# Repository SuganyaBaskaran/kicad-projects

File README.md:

# kicad-projects
Portfolio, learning and practice attempts using KiCAD.

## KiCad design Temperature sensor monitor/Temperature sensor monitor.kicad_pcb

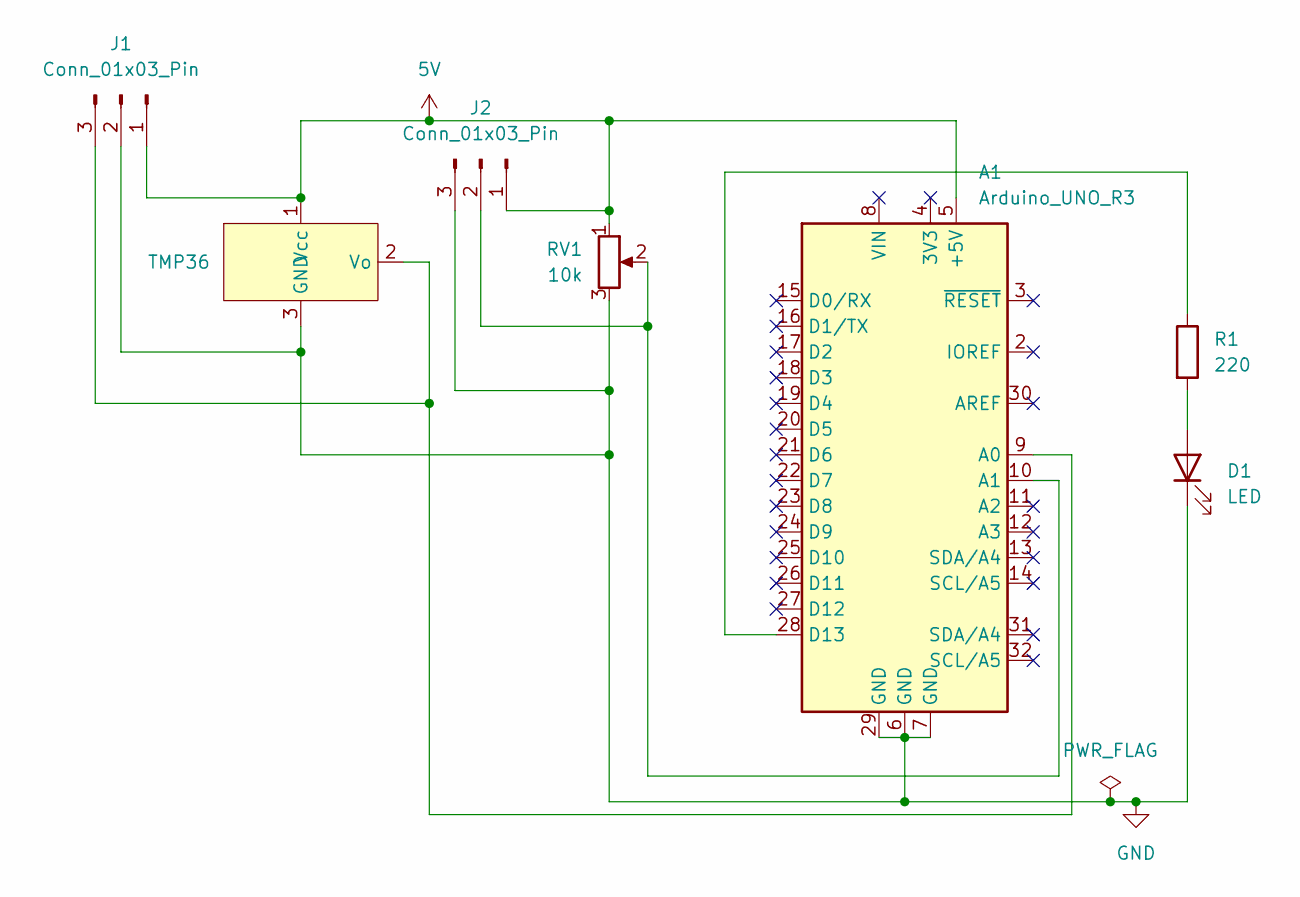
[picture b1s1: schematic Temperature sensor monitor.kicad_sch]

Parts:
A1: Arduino_UNO_R3
D1: LED; LED_D5.0mm
J1, J2: Conn_01x03_Pin; PinHeader_1x03_P2.54mm_Vertical
R1: 220; R_Axial_DIN0207_L6.3mm_D2.5mm_P7.62mm_Horizontal
RV1: 10k; Potentiometer_Bourns_3386P_Vertical
U1: TMP36; TO-92

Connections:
5V: A1.5 (+5V), J1.1, J2.1, RV1.1, U1.1 (Vcc)
GND: A1.6 (GND), A1.7 (GND), A1.29 (GND), D1.1 (K), J1.2, J2.3, RV1.3, U1.3 (GND)
unnamed: A1.9 (A0), J1.3, U1.2 (Vo)
unnamed: A1.10 (A1), J2.2, RV1.2
unnamed: A1.28 (D13), R1.1
unnamed: D1.2 (A), R1.2

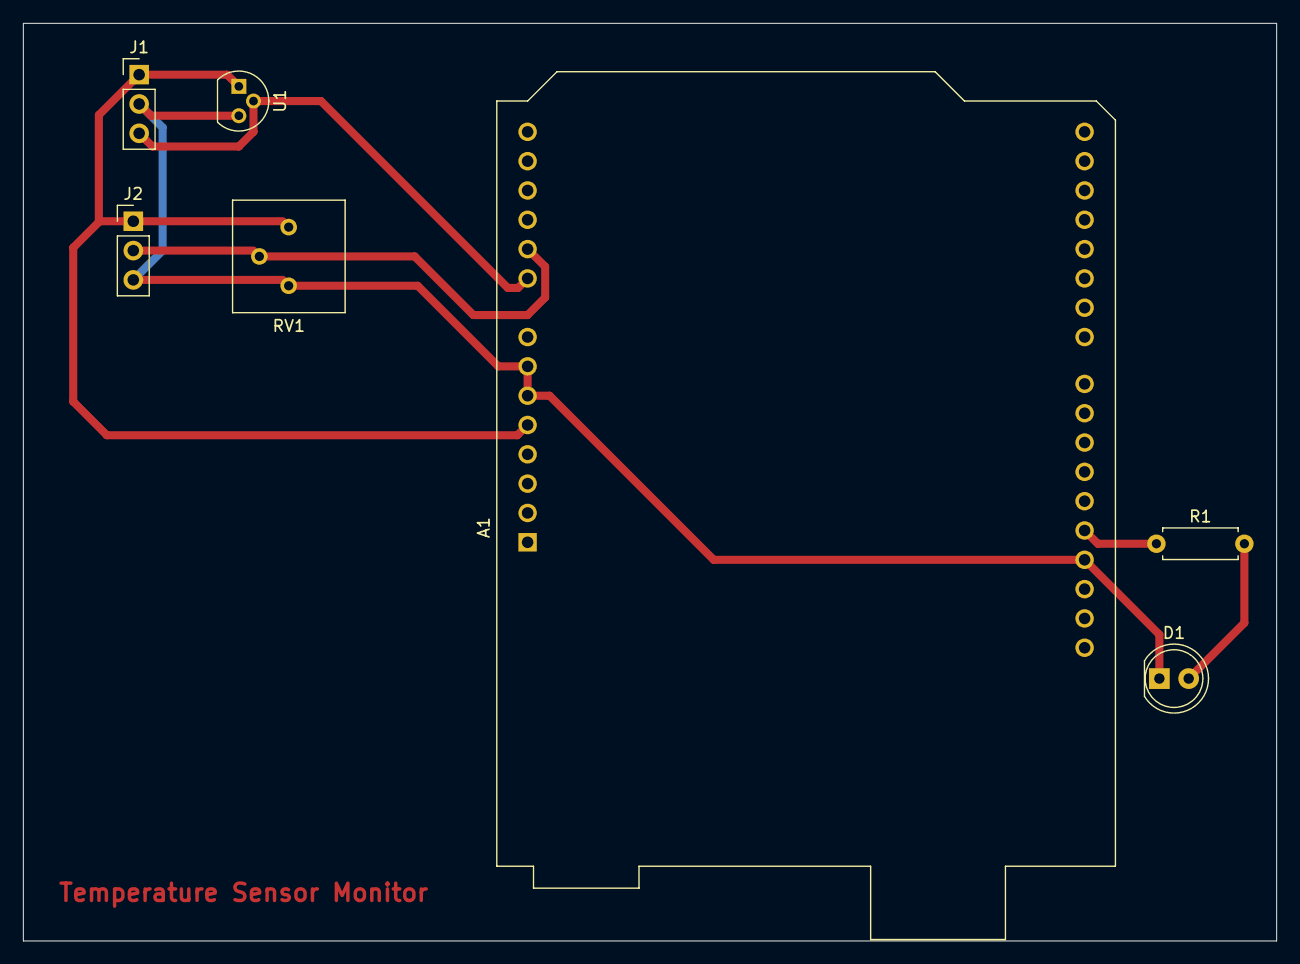
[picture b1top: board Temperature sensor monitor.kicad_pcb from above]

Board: 4 copper layers, 108.6 x 79.5 mm, 7 parts (0 on the bottom side), 6 nets.

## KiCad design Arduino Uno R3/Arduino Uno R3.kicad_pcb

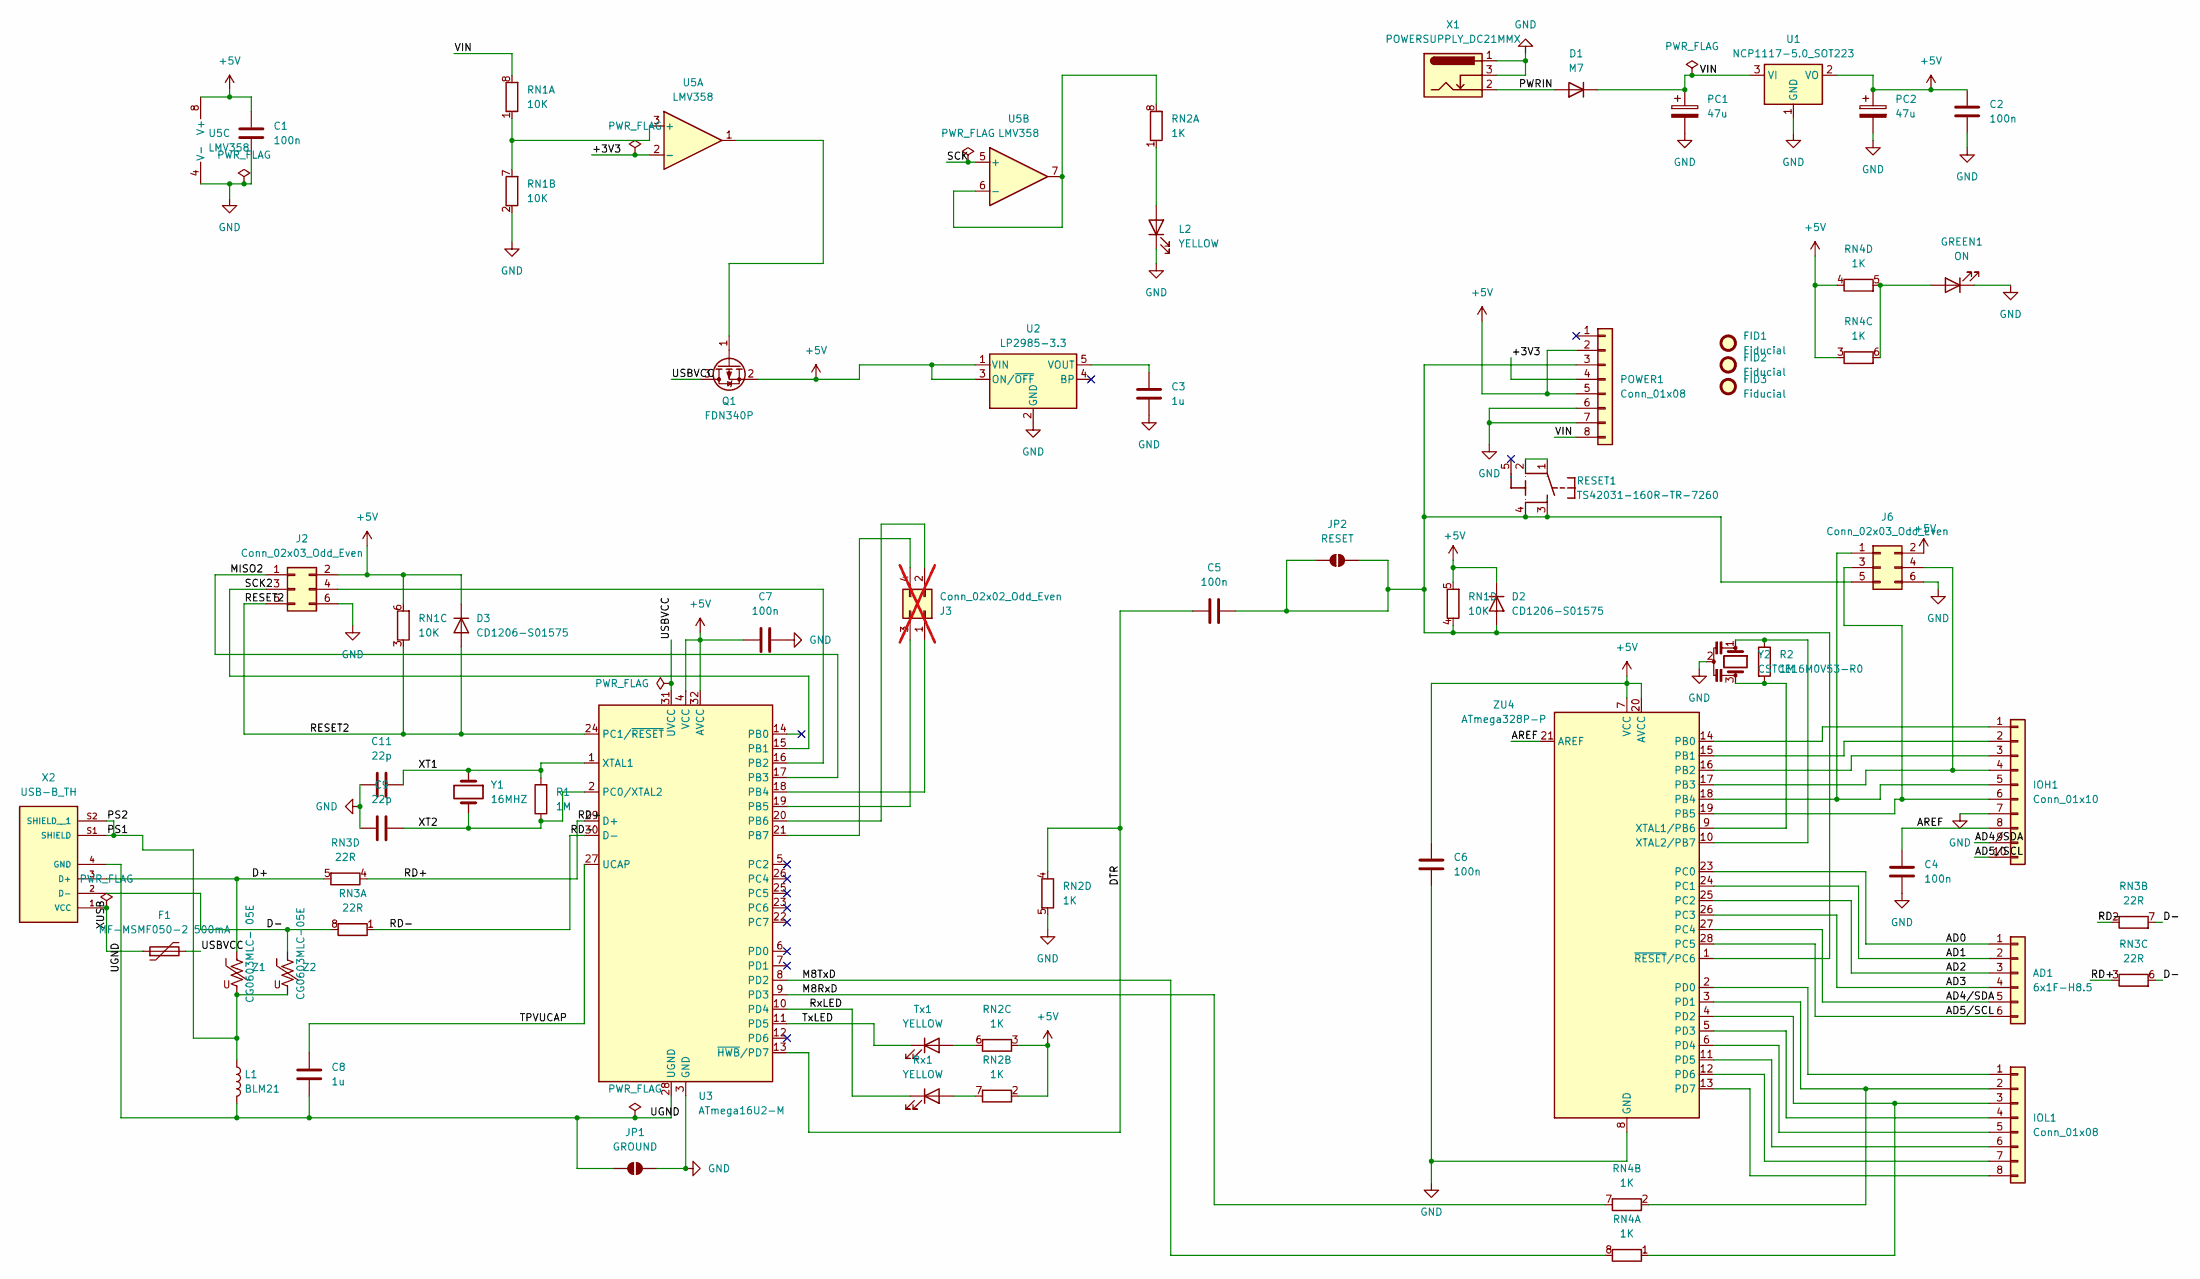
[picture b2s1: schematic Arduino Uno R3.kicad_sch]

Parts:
AD1: 6x1F-H8.5; PinSocket_1x06_P2.54mm_Vertical
C1, C2, C4, C5, C6, C7: 100n; C_0603_1608Metric
C3, C8: 1u; C_0603_1608Metric
C9, C11: 22p; C_0603_1608Metric
D1: M7; D_SMB
D2, D3: CD1206-S01575; D_1206_3216Metric
F1: MF-MSMF050-2 500mA; FUSM4632X85
FID1, FID2, FID3: Fiducial; Fiducial_1mm_Mask3mm
GREEN1: ON; LED_0805_2012Metric
IOH1: Conn_01x10; PinSocket_1x10_P2.54mm_Vertical
IOL1: Conn_01x08; PinSocket_1x08_P2.54mm_Vertical
J2, J6: Conn_02x03_Odd_Even; PinHeader_2x03_P2.54mm_Vertical
J3: Conn_02x02_Odd_Even; PinHeader_2x02_P2.54mm_Vertical; not fitted
JP1: GROUND; SolderJumper-2_P1.3mm_Open_Pad1.0x1.5mm
JP2: RESET; SolderJumper-2_P1.3mm_Open_Pad1.0x1.5mm
L1: BLM21; L_0805_2012Metric
L2: YELLOW; LED_0805_2012Metric
PC1, PC2: 47u; CP_Elec_6.3x4.9
POWER1: Conn_01x08; PinSocket_1x08_P2.54mm_Vertical
Q1: FDN340P; SOT-23
R1, R2: 1M; R_0603_1608Metric
RESET1: TS42031-160R-TR-7260; TS42
RN1: 10K; R_Array_Concave_4x0603
RN2, RN4: 1K; R_Array_Concave_4x0603
RN3: 22R; R_Array_Concave_4x0603
Rx1: YELLOW; LED_0805_2012Metric
Tx1: YELLOW; LED_0805_2012Metric
U1: NCP1117-5.0_SOT223; SOT-223-3_TabPin2
U2: LP2985-3.3; SOT-23-5
U3: ATmega16U2-M; QFN-32-1EP_5x5mm_P0.5mm_EP3.6x3.6mm
U5: LMV358; TSSOP-8_4.4x3mm_P0.65mm
X1: POWERSUPPLY_DC21MMX; BarrelJack_Horizontal
X2: USB-B_TH; AMPHENOL_61729-1011BLF; PARTREV AB
Y1: 16MHZ; Crystal_HC49-U_Vertical
Y2: CSTCE16M0V53-R0; Resonator_SMD_Murata_CSTxExxV-3Pin_3.0x1.1mm
Z1: CG0603MLC- 05E; VARC1608X56N
Z2: CG0603MLC-05E; VARC1608X56N
ZU4: ATmega328P-P; DIP-28_W7.62mm

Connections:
+5V: C1.1, C2.1, C6.1, C7.1, D2.1 (K), D3.1 (K), J2.2, J6.2, PC2.1, POWER1.2, POWER1.5, Q1.2 (S), RN1.5 (R4.2), RN1.6 (R3.2), RN2.2 (R2.1), RN2.3 (R3.1), RN4.3 (R3.1), RN4.4 (R4.1), U1.2 (VO), U2.1 (VIN), U2.3 (ON/~OFF), U3.4 (VCC), U3.32 (AVCC), U5.8 (V+), ZU4.7 (VCC), ZU4.20 (AVCC)
/+3V3: POWER1.4, U5.2 (-)
/AD0: AD1.1, ZU4.23 (PC0)
/AD1: AD1.2, ZU4.24 (PC1)
/AD2: AD1.3, ZU4.25 (PC2)
/AD3: AD1.4, ZU4.26 (PC3)
/AD4/SDA: AD1.5, IOH1.9, ZU4.27 (PC4)
/AD5/SCL: AD1.6, IOH1.10, ZU4.28 (PC5)
/AREF: C4.1, IOH1.8, ZU4.21 (AREF)
/D+: RN3.5 (R4.2), X2.3 (D+), Z1.1
/D-: RN3.6 (R3.2), RN3.7 (R2.2), RN3.8 (R1.2), X2.2 (D-), Z2.1
/DTR: C5.1, RN2.4 (R4.1), U3.13 (~HWB/PD7)
/M8RxD: RN4.7 (R2.2), U3.9 (PD3)
/M8TxD: RN4.8 (R1.2), U3.8 (PD2)
/MISO2: J2.1, U3.17 (PB3)
/PS1: L1.1, X2.S1 (SHIELD), X2.S2 (SHIELD__1), Z1.2, Z2.2
/PWRIN: D1.2 (A), X1.2
/RD+: RN3.3 (R3.1), RN3.4 (R4.1), U3.29 (D+)
/RD-: RN3.1 (R1.1), RN3.2 (R2.1), U3.30 (D-)
/RESET2: D3.2 (A), J2.5, RN1.3 (R3.1), U3.24 (PC1/~RESET)
/RxLED: Rx1.1 (K), U3.10 (PD4)
/SCK: U5.5 (+)
/SCK2: J2.3, U3.15 (PB1)
/TPVUCAP: C8.1, U3.27 (UCAP)
/TxLED: Tx1.1 (K), U3.11 (PD5)
/UGND: C8.2, JP1.1 (A), L1.2, U3.28 (UGND), X2.4 (GND)
/USBVCC: F1.2, Q1.3 (D), U3.31 (UVCC)
/VIN: D1.1 (K), PC1.1, POWER1.8, RN1.8 (R1.2), U1.3 (VI)
/XT1: C11.2, R1.2, U3.1 (XTAL1), Y1.1
/XT2: C9.2, R1.1, U3.2 (PC0/XTAL2), Y1.2
/XUSB: F1.1, X2.1 (VCC)
GND: C1.2, C2.2, C3.2, C4.2, C6.2, C7.2, C9.1, C11.1, GREEN1.1 (K), IOH1.7, J2.6, J6.6, JP1.2 (B), L2.1 (K), PC1.2, PC2.2, POWER1.6, POWER1.7, RN1.2 (R2.1), RN2.5 (R4.2), U1.1 (GND), U2.2 (GND), U3.3 (GND), U3.33 (GND), U5.4 (V-), X1.1, X1.3, Y2.2, ZU4.8 (GND), ZU4.22 (GND)
unnamed: C5.2, D2.2 (A), J6.5, JP2.1 (A), JP2.2 (B), POWER1.3, RESET1.3, RESET1.4, RN1.4 (R4.1), ZU4.1 (~RESET/PC6)
unnamed: GREEN1.2 (A), RN4.5 (R4.2), RN4.6 (R3.2)
unnamed: IOH1.1, ZU4.14 (PB0)
unnamed: IOH1.2, ZU4.15 (PB1)
unnamed: IOH1.3, ZU4.16 (PB2)
unnamed: IOH1.4, J6.4, ZU4.17 (PB3)
unnamed: IOH1.5, J6.1, ZU4.18 (PB4)
unnamed: IOH1.6, J6.3, ZU4.19 (PB5)
unnamed: IOL1.1, ZU4.2 (PD0)
unnamed: IOL1.2, RN4.2 (R2.1), ZU4.3 (PD1)
unnamed: IOL1.3, RN4.1 (R1.1), ZU4.4 (PD2)
unnamed: IOL1.4, ZU4.5 (PD3)
unnamed: IOL1.5, ZU4.6 (PD4)
unnamed: IOL1.6, ZU4.11 (PD5)
unnamed: IOL1.7, ZU4.12 (PD6)
unnamed: IOL1.8, ZU4.13 (PD7)
unnamed: J2.4, U3.16 (PB2)
unnamed: J3.1, U3.18 (PB4)
unnamed: J3.2, U3.20 (PB6)
unnamed: J3.3, U3.19 (PB5)
unnamed: J3.4, U3.21 (PB7)
unnamed: L2.2 (A), RN2.1 (R1.1)
unnamed: Q1.1 (G), U5.1
unnamed: RESET1.1, RESET1.2
unnamed: RN1.1 (R1.1), RN1.7 (R2.2), U5.3 (+)
unnamed: RN2.8 (R1.2), U5.6 (-), U5.7
unnamed: RN2.7 (R2.2), Rx1.2 (A)
unnamed: RN2.6 (R3.2), Tx1.2 (A)
unnamed: C3.1, U2.5 (VOUT)
unnamed: R2.2, Y2.3, ZU4.9 (XTAL1/PB6)
unnamed: R2.1, Y2.1, ZU4.10 (XTAL2/PB7)

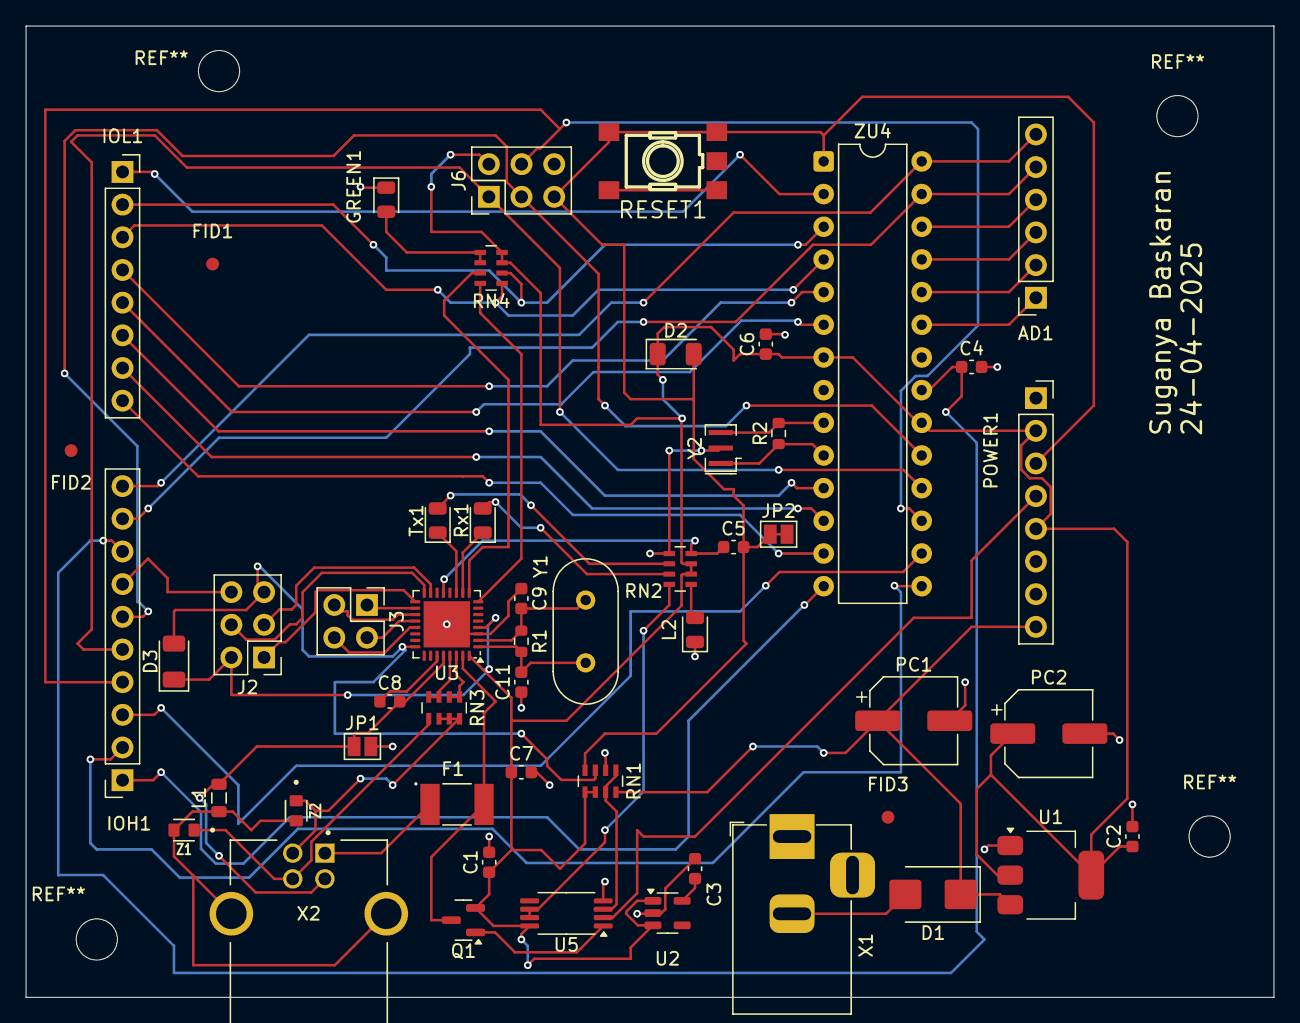
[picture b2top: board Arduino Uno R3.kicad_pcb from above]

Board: 2 copper layers, 97.0 x 75.5 mm, 52 parts (0 on the bottom side), 62 nets.

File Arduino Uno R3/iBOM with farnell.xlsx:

Ref | Value | Footprint | Quantity | Farnell id | SMD/THT
C1, C2, C4, C5, C6, C7 | 100n | C_0603_1608Metric | 6 | 3288318 | SMD
C3, C8 | 1u | C_0603_1608Metric | 2 | 2118128 | SMD
C9, C11 | 22p | C_0603_1608Metric | 2 | 3508850 | SMD
R1, R2 | 1M | R_0603_1608Metric | 2 | 3579860 | SMD
L2, Rx1, Tx1 | YELLOW | LED_0805_2012Metric | 3 | 1318246 | SMD
L1 | BLM21 | L_0805_2012Metric | 1 | 3227824 | SMD
D2, D3 | CD1206-S01575 | D_1206_3216Metric | 2 | 652-CD1206-S01575(Mouser) | SMD
D1 | M7 | D_SMB | 1 | 3127427 | SMD
U1 | NCP1117-5.0_SOT223 | SOT-223-3_TabPin2 | 1 | 2112617 | SMD
U2 | LP2985-3.3 | SOT-23-5 | 1 | 3007616 | SMD
U3 | ATmega16U2-M | QFN-32-1EP_5x5mm_P0.5mm_EP3.6x3.6mm | 1 | 2810000 | SMD
U5 | LMV358 | TSSOP-8_4.4x3mm_P0.65mm | 1 | 2806805 | SMD
Y1 | 16MHZ | Crystal_HC49-U_Vertical | 1 | 9712860 | THT
Y2 | CSTCE16M0V53-R0 | Resonator_SMD_Murata_CSTxExxV-3Pin_3.0x1.1mm | 1 | 2443265 | SMD
X1 | POWERSUPPLY_DC21MMX | BarrelJack_Horizontal | 1 | 224959 | THT
X2 | USB-B_TH | AMPHENOL_61729-1011BLF | 1 | 2668483 | THT
F1 | MF-MSMF050-2 500mA | FUSM4632X85 | 1 | 9350314 | SMD
IOL1, POWER1 | Conn_01x08 | PinSocket_1x08_P2.54mm_Vertical | 2 | 3583755 | THT
PC1, PC2 | 47u | CP_Elec_6.3x4.9 | 2 | 3227549 | SMD
RN2, RN4 | 1K | R_Array_Concave_4x0603 | 2 | 2060162 | SMD
AD1 | 6x1F-H8.5 | PinSocket_1x06_P2.54mm_Vertical | 1 | 2827893 | THT
GREEN1 | ON | LED_0805_2012Metric | 1 | 2290331 | SMD
IOH1 | Conn_01x10 | PinSocket_1x10_P2.54mm_Vertical | 1 | 1841230 | THT
Q1 | FDN340P | SOT-23 | 1 | 9846310 | SMD
RESET1 | TS42031-160R-TR-7260 | TS42 | 1 | 506-FSMSMLPATR(Mouser) | SMD
RN1 | 10K | R_Array_Concave_4x0603 | 1 | 2060167 | SMD
RN3 | 22R | R_Array_Concave_4x0603 | 1 | 2060150 | SMD
Z1 | CG0603MLC-05E | VARC1608X56N | 1 | 1838966 | SMD
Z2 | CG0603MLC-05E | VARC1608X56N | 1 | 1838966 | SMD
ZU4 | ATmega328P-P | DIP-28_W7.62mm | 1 | 2443179 | THT
J2, J6 | Conn_02x03_Odd_Even | PinHeader_2x03_P2.54mm_Vertical | 2 | 2356131 | THT

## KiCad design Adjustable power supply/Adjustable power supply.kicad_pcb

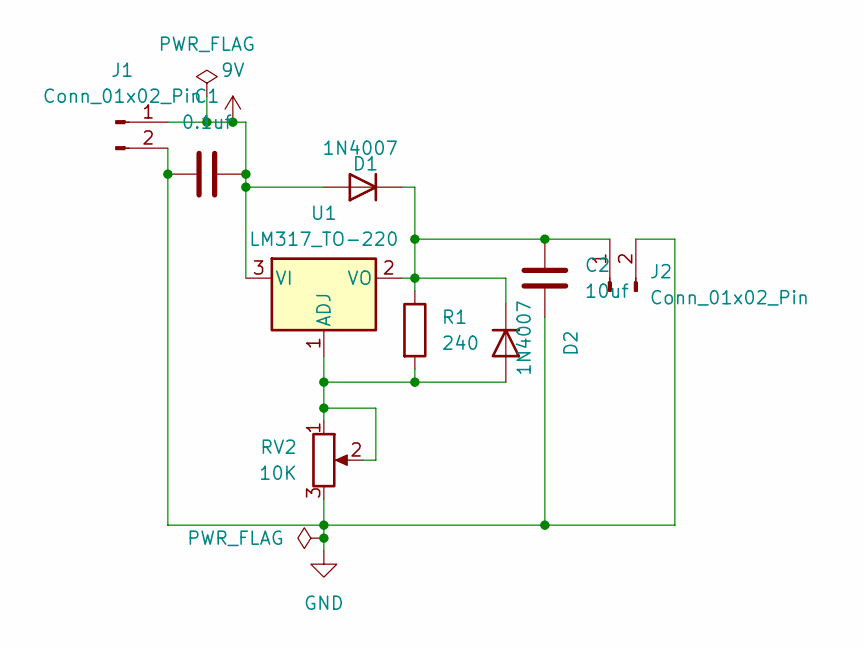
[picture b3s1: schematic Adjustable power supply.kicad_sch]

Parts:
C1: 0.1uf; C_Disc_D3.0mm_W1.6mm_P2.50mm
C2: 10uf; C_Disc_D3.0mm_W1.6mm_P2.50mm
D1, D2: 1N4007; D_DO-41_SOD81_P10.16mm_Horizontal
J1, J2: Conn_01x02_Pin; TerminalBlock_bornier-2_P5.08mm
R1: 240; R_Axial_DIN0207_L6.3mm_D2.5mm_P2.54mm_Vertical
RV2: 10K; Potentiometer_Alpha_RD901F-40-00D_Single_Vertical
U1: LM317_TO-220; TO-220-3_Vertical

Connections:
9V: C1.2, D1.2 (A), J1.1, U1.3 (VI)
GND: C1.1, C2.1, J1.2, J2.2, RV2.3
unnamed: C2.2, D1.1 (K), D2.1 (K), J2.1, R1.1, U1.2 (VO)
unnamed: D2.2 (A), R1.2, RV2.1, RV2.2, U1.1 (ADJ)

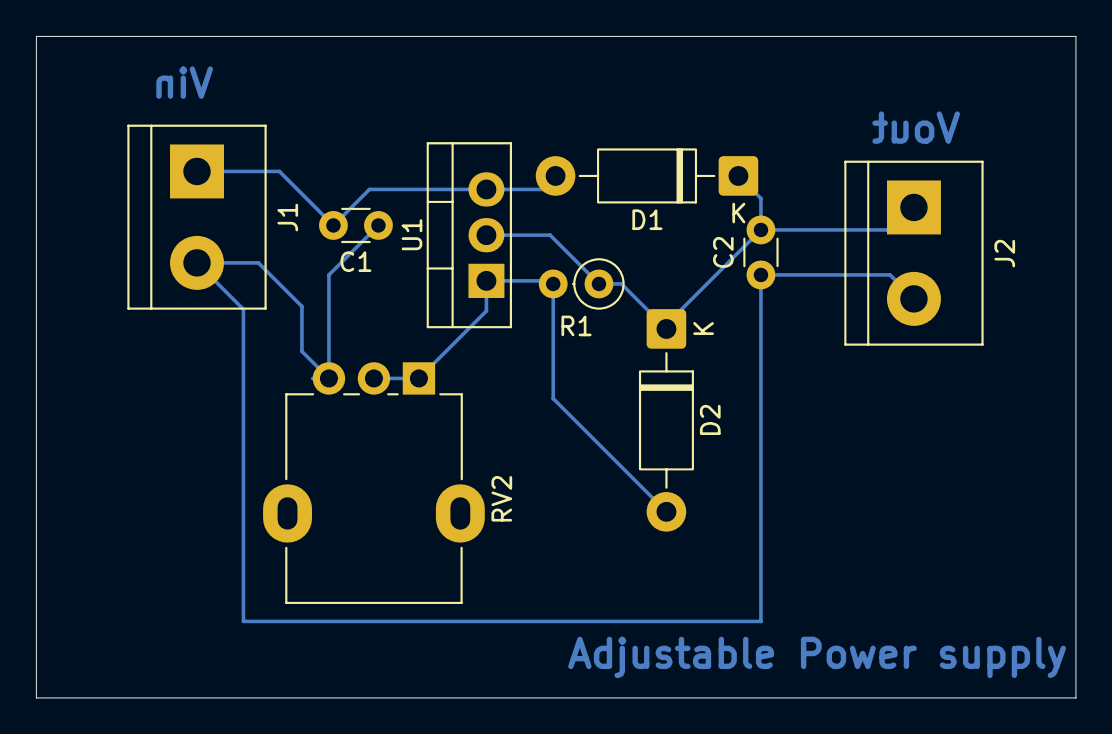
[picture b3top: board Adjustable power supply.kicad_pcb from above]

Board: 2 copper layers, 57.8 x 36.8 mm, 9 parts (0 on the bottom side), 4 nets.

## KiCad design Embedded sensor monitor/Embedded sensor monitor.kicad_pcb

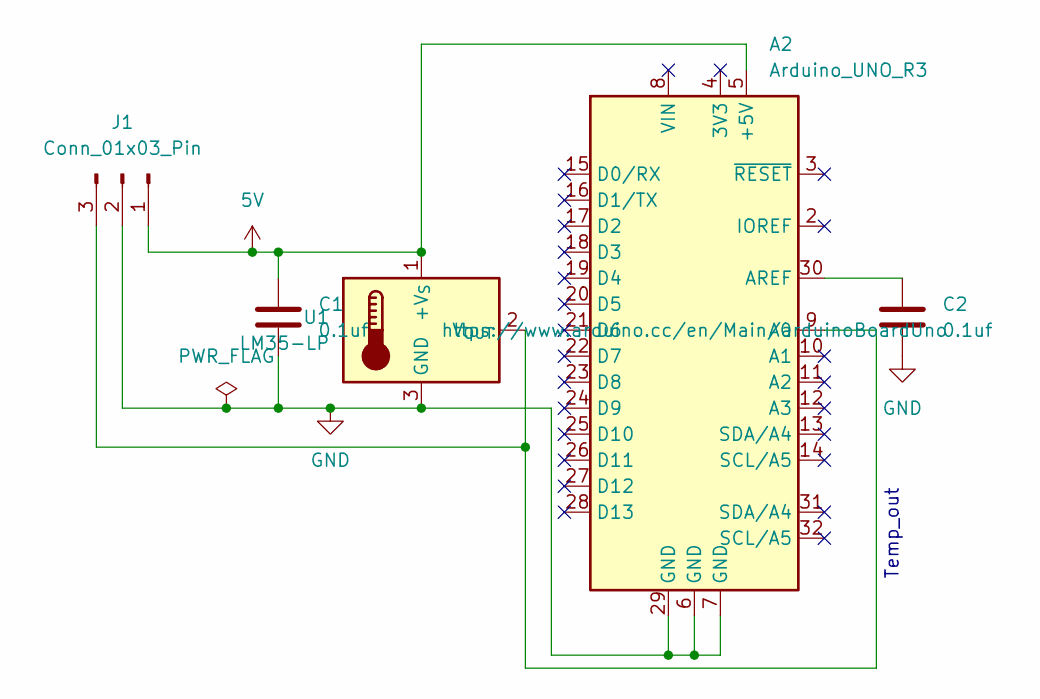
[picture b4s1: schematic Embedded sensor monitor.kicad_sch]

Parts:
A2: Arduino_UNO_R3
C1, C2: 0.1uf; C_Radial_D5.0mm_H5.0mm_P2.00mm
J1: Conn_01x03_Pin; FanPinHeader_1x03_P2.54mm_Vertical
U1: LM35-LP; TO-92_Inline

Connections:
5V: A2.5 (+5V), C1.1, J1.1, U1.1 (+V_{S})
GND: A2.6 (GND), A2.7 (GND), A2.29 (GND), C1.2, C2.2, J1.2, U1.3 (GND)
unnamed: A2.9 (A0), J1.3, U1.2 (V_{OUT})
unnamed: A2.30 (AREF), C2.1

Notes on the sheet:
Temp_out

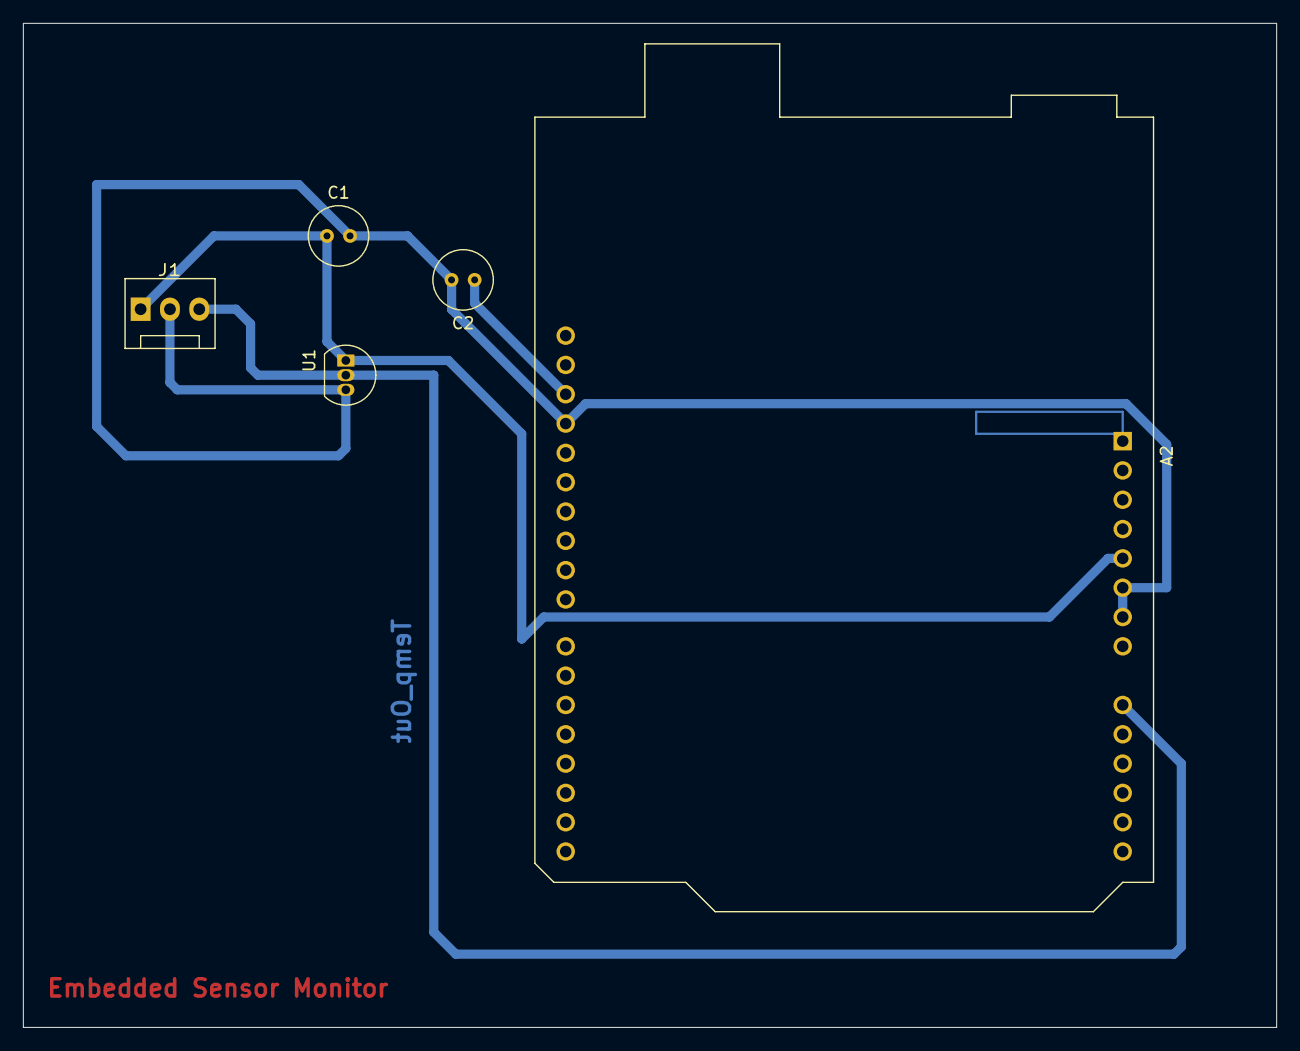
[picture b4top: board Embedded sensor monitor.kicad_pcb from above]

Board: 2 copper layers, 108.6 x 87.0 mm, 5 parts (0 on the bottom side), 4 nets.

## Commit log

2026-03-28 commit first 2 projects
    commit first 2 projects
2026-03-28 test segment
    test segment
2026-03-28 reverse change
2026-03-28 arduino uno project added
2026-05-10 Temperature sensor Monitor
    temperature sensor
